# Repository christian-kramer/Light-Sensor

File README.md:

# Light-Sensor
My first project exploring the process of taking a design from my head to production.

---

This repo is a continuation of my PIC16F887-Familiarization project. In that project, what began with blinking lights morphed into something utilitarian: turn on an LED when the ambient light gets darker than it was. After breadboarding a working prototype with my 44-pin Demo Board, I decided to take it a step further and try manufacturing the prototype as a finished PCB.

There were two parts to consider: hardware and software. First of all, I didn't need to use the 44-pin PIC16F887 in the production boards... I needed to find the PIC with the least amount of bells and whistles that still do what I wanted. I only needed 1 Analog-to-Digital Converter for the light sensor, and 1 output pin for the LED, so I knew I could probably get away with a bottom-of-the-barrel PIC. I went to Microchip's website, sorted price by "lowest first", and went with the first PIC that had an ADC: the PIC10F220. A whopping 6 pins, 16 bytes of SRAM, and 375 bytes of Flash storage. But, with all of the support circuitry built-in, and an 8-bit ADC, all for $0.40... you just can't beat it.

Once the microcontroller selection process was out of the way, I whipped up a KiCAD mockup of my breadboard circuit, mapped to the PIC10F220 pins instead of my demo board. Unlike my prototype, the finished product would have 2 potential power supplies... the battery, and the PICkit2 programmer. In order to isolate them, I used a 3 position switch as the power-supply selector. Left pin went to the battery, right pin went to the J1 programming header, and middle pin went to VCC. That way there was physically no way the two power sources could ever mix.

After the conceptual circuit diagram was made, I had to think about how it should look laid out on an actual board. I wanted the device to be small, not much bigger than the battery. I took the footprint of the battery holder, and made a 3.5cm x 3cm rectangular board outline around it, making sure to offset it slightly for the through-hole resistors I'd need to find a place for. I laid those out first, followed by the programming header, the PIC, decoupling capacitor, LED, programming jumper, and switch. I aligned these components as close to the perimeter of the board as possible, because since the beginning I had a vision of a QR code linking back to my github planted in the middle... acting as a sort of business card. (Hello, btw, if that is how you found this)

With everything looking ship-shape, I placed the order for the parts, and followed [JLCPCB's insctructions](https://support.jlcpcb.com/article/44-how-to-export-kicad-pcb-to-gerber-files) for exporting the gerber files correctly, and sent them off to be fabricated.

Here is the finished product:

---

## But that's not all... (Troubleshooting)

All was not completely well, however. The boards were not acting like the prototype. They didn't work immediately when they were turned on... only after the MCLR pin was manually pulled low. This raised some concerning red flags, namely that there could be something wrong electrically. I noticed that the battery holder was not making adequate contact with the battery, causing the microcontroller to randomly reset itself. But it was still exhibiting the same erroneous behavior even after putting a thicker battery in it... I looked to the datasheet for more advice. There seemed to be no major discrepancies between what the Power-On Reset and the MCLR Reset did as far as resetting the microcontroller... so maybe the Power-On Reset routine wasn't happening at all? According to datasheet figure 8-5, if Vdd doesn't reach its maximum within a certain period of time, the microcontroller will not reset properly. So I pulled off the decoupling capacitor, thinking the battery couldn't charge it quickly enough... but the behavior was unchanged. It still needed to be manually reset to work. Then I thought... what if it was just a software bug all along? Looking at my code, I was taking the first sample from the light sensor and treating it as the "baseline" for all other readings to be compared to. But, as I remembered from before, the oscilloscope showed that the output from the photoresistor was extremely jumpy; often it would read much lower than it should. So I added a function to take 255 samples over the course of about half a second, choose the largest value of those samples, and use that as baseline... and boom! It worked perfectly. The microcontroller was just using bad data all along. Nothing was wrong electrically, just a bug.

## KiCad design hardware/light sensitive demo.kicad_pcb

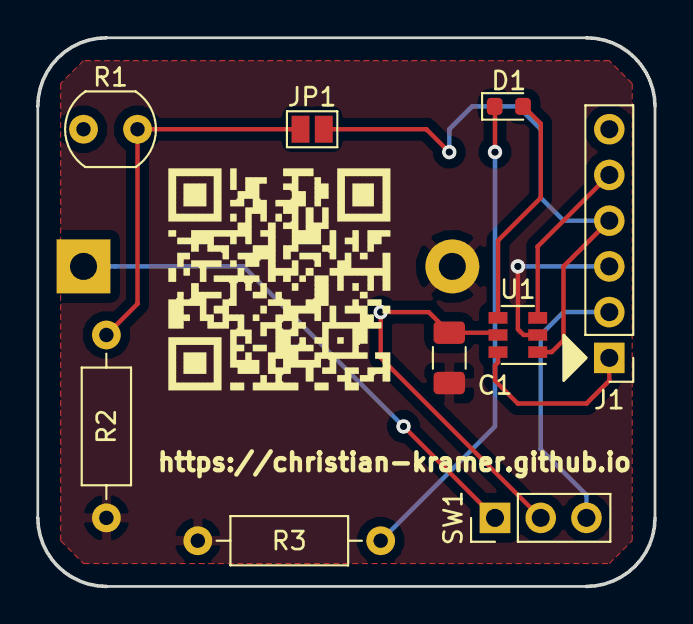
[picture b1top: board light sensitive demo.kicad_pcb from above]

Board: 2 copper layers, 34.3 x 30.5 mm, 11 parts (1 on the bottom side), 10 nets.

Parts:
BT1: Battery_Cell; BatteryHolder_Keystone_103_1x20mm
C1: 0.1μF; C_1206_3216Metric
D1: LED; LED_0603_1608Metric
J1: Conn_01x06_Female; PinHeader_1x06_P2.54mm_Vertical
JP1: Jumper_NO_Small; SolderJumper-2_P1.3mm_Open_Pad1.0x1.5mm
QR: QR
R1: R_PHOTO; R_LDR_5.0x4.1mm_P3mm_Vertical
R2: 10k; R_Axial_DIN0207_L6.3mm_D2.5mm_P10.16mm_Horizontal
R3: 100; R_Axial_DIN0207_L6.3mm_D2.5mm_P10.16mm_Horizontal
SW1: SW_SPDT; PinHeader_1x03_P2.54mm_Vertical
U1: PIC10F220-IOT; SOT-23-6

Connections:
GND: BT1.2, C1.2, J1.3, R2.2, R3.2, U1.2
unnamed: BT1.1, SW1.1
unnamed: D1.1, R3.1
unnamed: D1.2, U1.4
unnamed: J1.1, U1.6
unnamed: J1.2, SW1.3
unnamed: J1.4, JP1.2, U1.1
unnamed: J1.5, U1.3
unnamed: JP1.1, R1.2, R2.1
VCC: C1.1, R1.1, SW1.2, U1.5

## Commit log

2018-08-28 Changed adjustment potentiometer to push-button
2018-08-30 Refactored circuit to use optoisolator at mosfet gate
2018-09-19 Final version before sending off to PCB fabricator
2018-09-21 Preliminary port from PIC16F887
2018-09-24 reliably working
2018-09-24 updated compiled files for production run
2018-09-25 Recap of project journey
2018-09-25 added troubleshooting anecdote
2018-09-25 fixed markdown formatting error
2018-09-25 swapped thematic break and header
2018-09-25 Added 3d view of KiCAD layout
2018-09-25 corrected position of 3d KiCAD footprint view
